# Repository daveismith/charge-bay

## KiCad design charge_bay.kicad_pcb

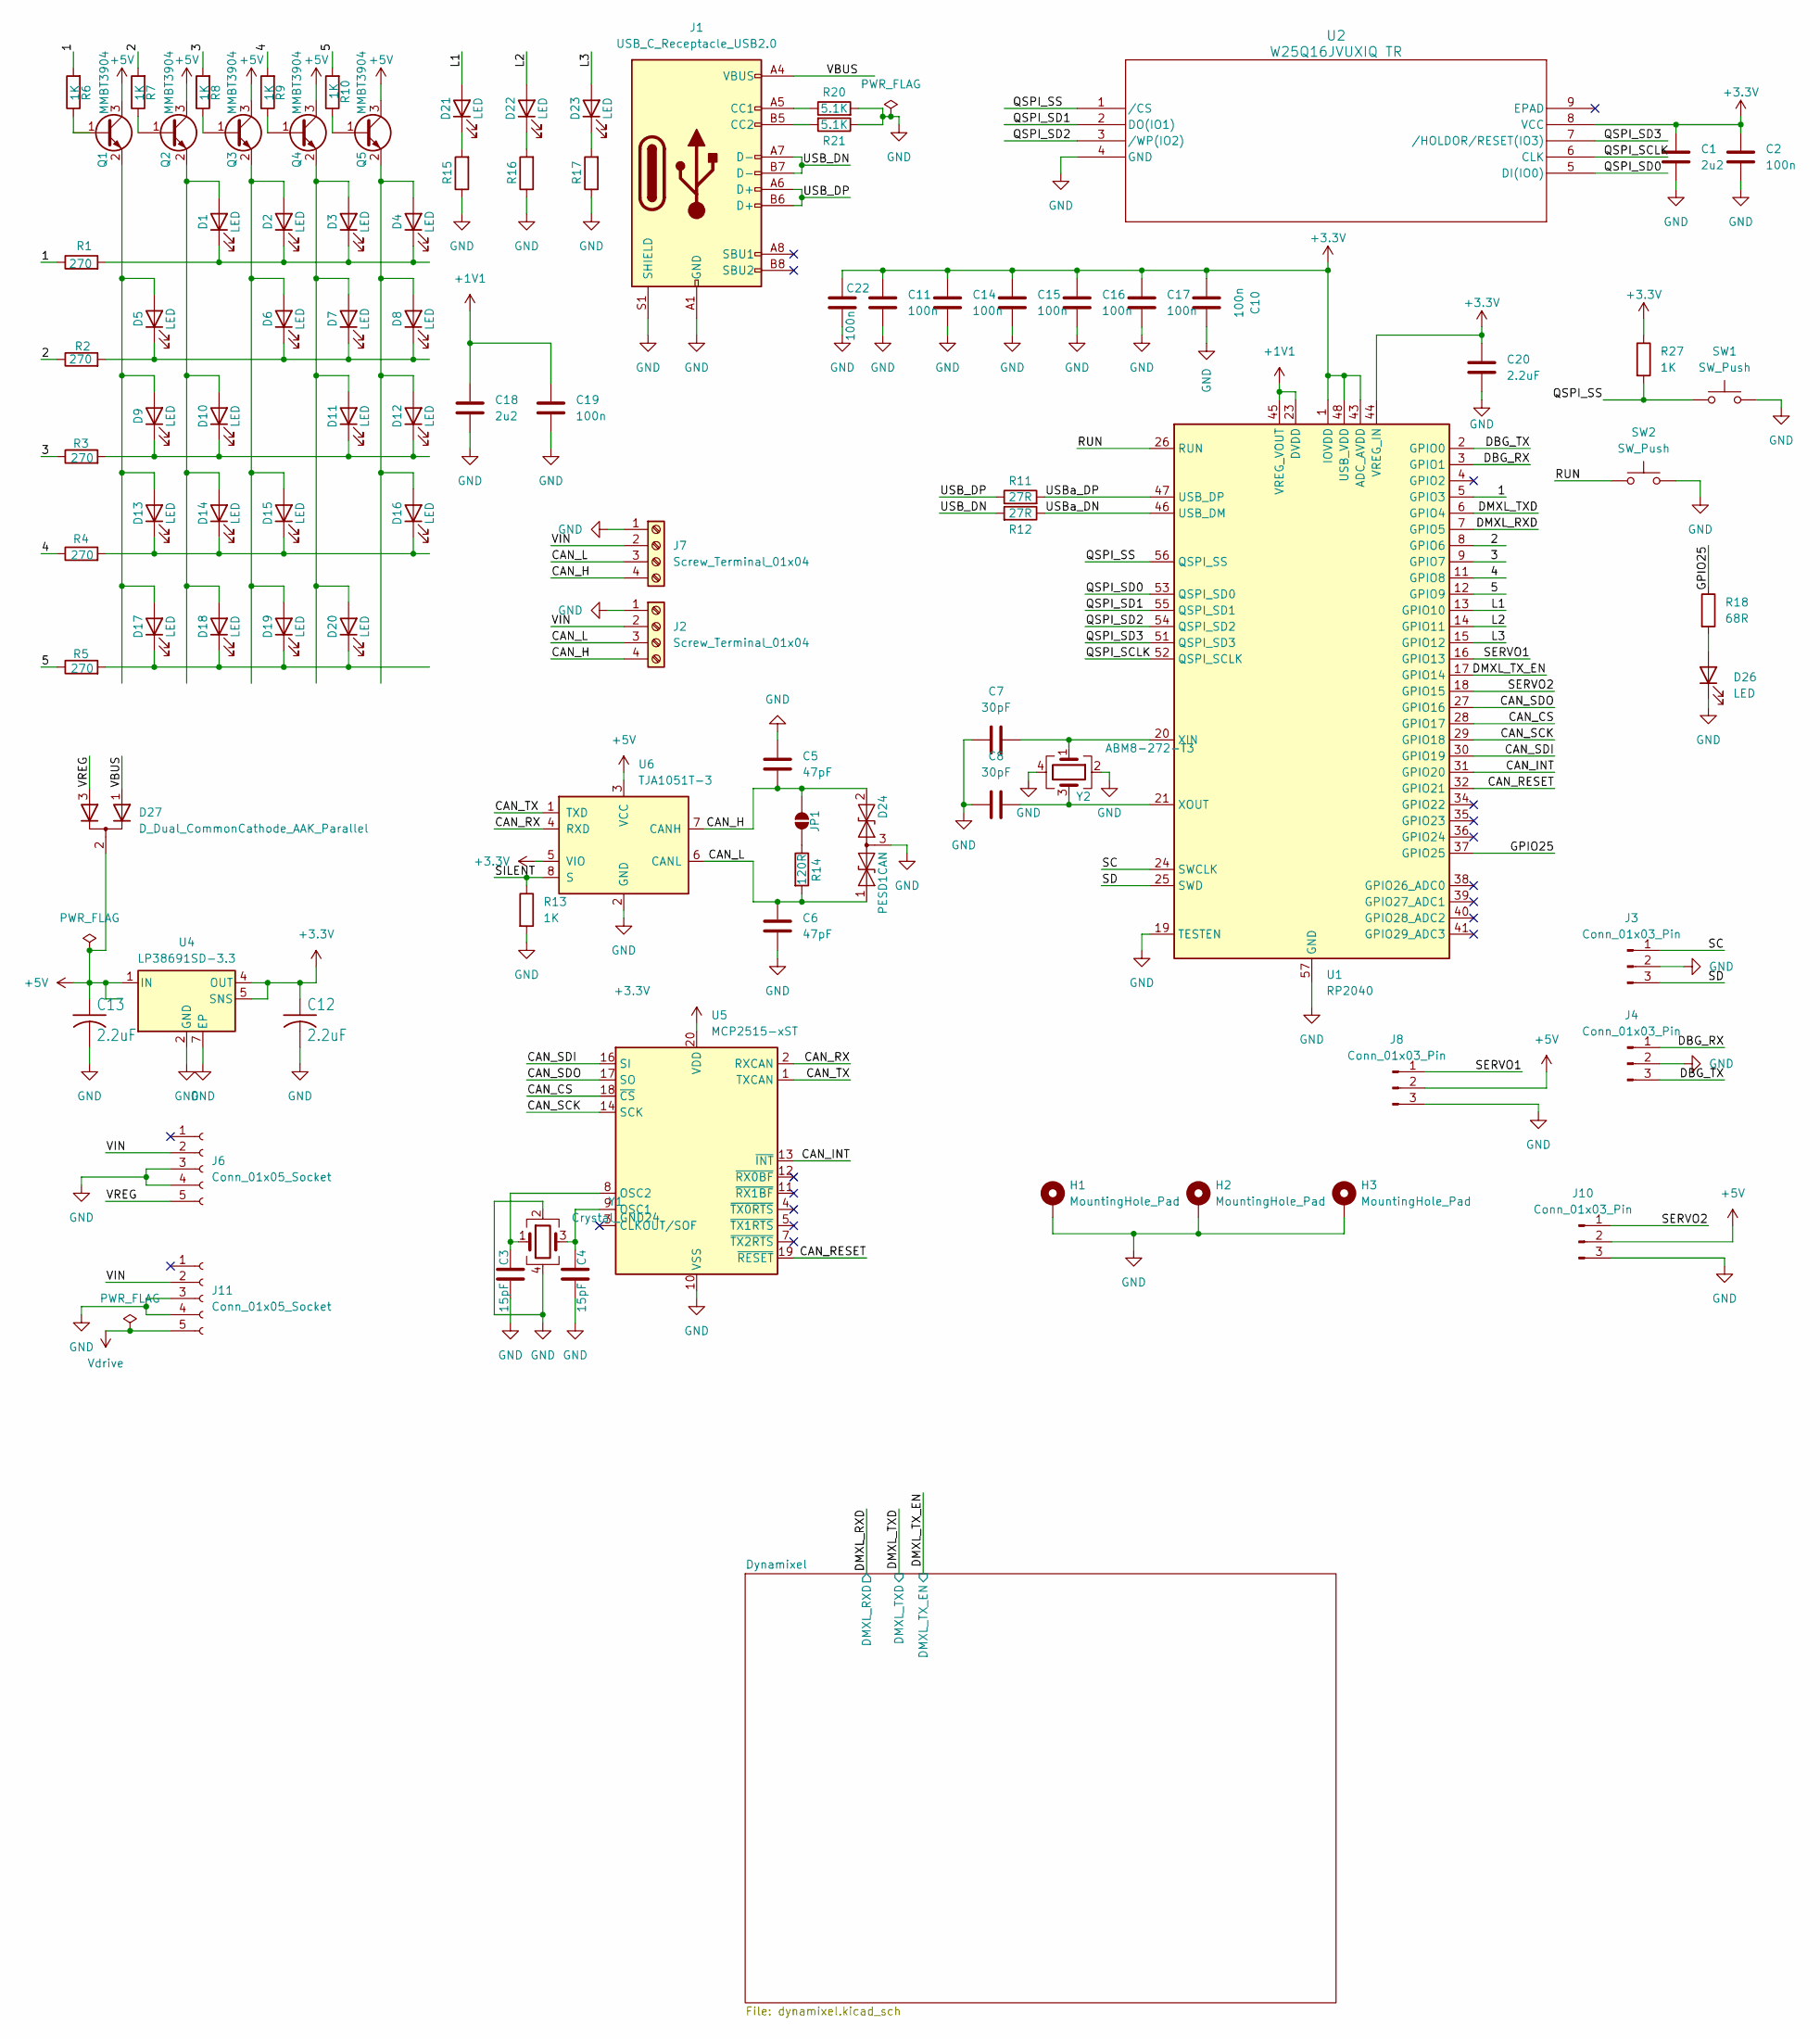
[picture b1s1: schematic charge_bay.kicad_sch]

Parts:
C1, C18: 2u2; C_0402_1005Metric; JLCPCB C12530
C2, C10, C11, C14, C15, C16, C17, C19, C22: 100n; C_0402_1005Metric; JLCPCB C1525
C3, C4: 15pF; C_0603_1608Metric; JLCPCB C1644
C5, C6: 47pF; C_0603_1608Metric; JLCPCB C1671
C7, C8: 30pF; C_0603_1608Metric; JLCPCB C1658
C12, C20: 2.2uF; C_0402_1005Metric; JLCPCB C12530
C13: 2.2uF; C_0603_1608Metric; JLCPCB C23630
D1, D2, D3, D4, D5, D6, D7, D8, D9, D10, D11, D12, D13, D14, D15, D16, D17, D18, D19, D20, D21, D22, D23: LED; LED_D3.0mm
D24: PESD1CAN; SOT-23; JLCPCB C284094
D26: LED; LED_0603_1608Metric; JLCPCB C2286
D27: D_Dual_CommonCathode_AAK_Parallel; SOT-223-3_TabPin2; JLCPCB C260229
H1, H2, H3: MountingHole_Pad; MountingHole_3.2mm_M3_DIN965_Pad_TopBottom
J1: USB_C_Receptacle_USB2.0; USB_C_Receptacle_G-Switch_GT-USB-7010ASV; JLCPCB C2988369
J2, J7: Screw_Terminal_01x04; TerminalBlock_Phoenix_PT-1,5-4-3.5-H_1x04_P3.50mm_Horizontal
J3, J4: Conn_01x03_Pin; JST_SH_BM03B-SRSS-TB_1x03-1MP_P1.00mm_Vertical
J6, J11: Conn_01x05_Socket; PinSocket_1x05_P2.54mm_Vertical
J8, J10: Conn_01x03_Pin; PinHeader_1x03_P2.54mm_Vertical
JP1: SolderJumper_2_Open; SolderJumper-2_P1.3mm_Open_TrianglePad1.0x1.5mm
Q1, Q2, Q3, Q4, Q5: MMBT3904; SOT-23; JLCPCB C20526
R1, R2, R3, R4, R5: 270; R_0603_1608Metric; JLCPCB C22966
R6, R7, R8, R9, R10, R13, R15, R16, R17, R27: 1K; R_0402_1005Metric; JLCPCB C11702
R11, R12: 27R; R_0402_1005Metric; JLCPCB C25100
R14: 120R; R_0402_1005Metric; JLCPCB C25079
R18: 68R; R_0402_1005Metric; JLCPCB C25131
R20, R21: 5.1K; R_0402_1005Metric; JLCPCB C25905
SW1, SW2: SW_Push; SW_Push_1P1T_XKB_TS-1187A; JLCPCB C318884
U1: RP2040; QFN-56-1EP_7x7mm_P0.4mm_EP3.2x3.2mm; JLCPCB C2040
U2: W25Q16JVUXIQ TR; USON-8_UX_2x3x0p6_WIN; JLCPCB C2843335
U4: LP38691SD-3.3; WSON-6-1EP_3x3mm_P0.95mm; JLCPCB C2876186
U5: MCP2515-xST; TSSOP-20_4.4x6.5mm_P0.65mm; JLCPCB C15193
U6: TJA1051T-3; SOIC-8_3.9x4.9mm_P1.27mm; JLCPCB C38695
Y1: Crystal_GND24; Crystal_SMD_Abracon_ABM8G-4Pin_3.2x2.5mm; JLCPCB C13738
Y2: ABM8-272-T3; Crystal_SMD_Abracon_ABM8G-4Pin_3.2x2.5mm; JLCPCB C9002

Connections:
+1V1: C18.1, C19.1, U1.23 (DVDD), U1.45 (VREG_VOUT), U1.50 (DVDD)
+3.3V: C1.1, C2.1, C10.1, C11.2, C12.1, C14.2, C15.2, C16.2, C17.2, C20.1, C22.2, R27.1, U1.1 (IOVDD), U1.10 (IOVDD), U1.22 (IOVDD), U1.33 (IOVDD), U1.42 (IOVDD), U1.43 (ADC_AVDD), U1.44 (VREG_IN), U1.48 (USB_VDD), U1.49 (IOVDD), U2.8 (VCC), U4.4 (OUT), U4.5 (SNS), U5.20 (VDD), U6.5 (VIO); also elsewhere on the board
+5V: C13.1, D27.2 (K), J8.2, J10.2, Q1.3 (C), Q2.3 (C), Q3.3 (C), Q4.3 (C), Q5.3 (C), U4.1 (IN), U4.6 (IN), U6.3 (VCC); also elsewhere on the board
/1: R1.1, R6.2, U1.5 (GPIO3)
/2: R2.1, R7.2, U1.8 (GPIO6)
/3: R3.1, R8.2, U1.9 (GPIO7)
/4: R4.1, R9.2, U1.11 (GPIO8)
/5: R5.1, R10.2, U1.12 (GPIO9)
/CAN_CS: U1.28 (GPIO17), U5.18 (~CS)
/CAN_H: C5.2, D24.2 (A2), J2.4, J7.4, JP1.2 (B), U6.7 (CANH)
/CAN_INT: U1.31 (GPIO20), U5.13 (~INT)
/CAN_L: C6.1, D24.1 (A1), J2.3, J7.3, R14.2, U6.6 (CANL)
/CAN_RESET: U1.32 (GPIO21), U5.19 (~RESET)
/CAN_RX: U5.2 (RXCAN), U6.4 (RXD)
/CAN_SCK: U1.29 (GPIO18), U5.14 (SCK)
/CAN_SDI: U1.30 (GPIO19), U5.16 (SI)
/CAN_SDO: U1.27 (GPIO16), U5.17 (SO)
/CAN_TX: U5.1 (TXCAN), U6.1 (TXD)
/DBG_RX: J4.1, U1.3 (GPIO1)
/DBG_TX: J4.3, U1.2 (GPIO0)
/DMXL_RXD: U1.7 (GPIO5); also elsewhere on the board
/DMXL_TXD: U1.6 (GPIO4); also elsewhere on the board
/DMXL_TX_EN: U1.17 (GPIO14); also elsewhere on the board
/GPIO25: R18.1, U1.37 (GPIO25)
/L1: D21.2 (A), U1.13 (GPIO10)
/L2: D22.2 (A), U1.14 (GPIO11)
/L3: D23.2 (A), U1.15 (GPIO12)
/QSPI_SCLK: U1.52 (QSPI_SCLK), U2.6 (CLK)
/QSPI_SD0: U1.53 (QSPI_SD0), U2.5 (DI(IO0))
/QSPI_SD1: U1.55 (QSPI_SD1), U2.2 (DO(IO1))
/QSPI_SD2: U1.54 (QSPI_SD2), U2.3 (/WP(IO2))
/QSPI_SD3: U1.51 (QSPI_SD3), U2.7 (/HOLDOR/RESET(IO3))
/QSPI_SS: R27.2, SW1.1, U1.56 (QSPI_SS), U2.1 (/CS)
/RUN: SW2.1, U1.26 (RUN)
/SC: J3.1, U1.24 (SWCLK)
/SD: J3.3, U1.25 (SWD)
/SERVO1: J8.1, U1.16 (GPIO13)
/SERVO2: J10.1, U1.18 (GPIO15)
/SILENT: R13.1, U6.8 (S)
/USB_DN: J1.A7 (D-), J1.B7 (D-), R12.2
/USB_DP: J1.A6 (D+), J1.B6 (D+), R11.1
/USBa_DN: R12.1, U1.46 (USB_DM)
/USBa_DP: R11.2, U1.47 (USB_DP)
/VBUS: D27.1 (A), J1.A4 (VBUS), J1.A9 (VBUS), J1.B4 (VBUS), J1.B9 (VBUS)
/VIN: J2.2, J6.2, J7.2, J11.2
/VREG: D27.3 (A), J6.5
GND: C1.2, C2.2, C3.2, C4.2, C5.1, C6.2, C7.1, C8.1, C10.2, C11.1, C12.2, C13.2, C14.1, C15.1, C16.1, C17.1, C18.2, C19.2, C20.2, C22.1, D24.3 (common), D26.1 (K), H1.1, H2.1, H3.1, J1.A1 (GND), J1.A12 (GND), J1.B1 (GND), J1.B12 (GND), J1.S1 (SHIELD), J2.1, J3.2, J4.2, J6.3, J6.4, J7.1, J8.3, J10.3, J11.3, J11.4, R13.2, R15.1, R16.1, R17.1, R20.2, R21.1, SW1.2, SW2.2, U1.19 (TESTEN), U1.57 (GND), U2.4 (GND), U4.2 (GND), U4.7 (EP), U5.10 (VSS), U6.2 (GND), Y1.2, Y1.4, Y2.2, Y2.4; also elsewhere on the board
unnamed: D1.2 (A), D10.2 (A), D14.2 (A), D18.2 (A), Q2.2 (E)
unnamed: D1.1 (K), D2.1 (K), D3.1 (K), D4.1 (K), R1.2
unnamed: D5.1 (K), D6.1 (K), D7.1 (K), D8.1 (K), R2.2
unnamed: D9.1 (K), D10.1 (K), D11.1 (K), D12.1 (K), R3.2
unnamed: D3.2 (A), D7.2 (A), D11.2 (A), D20.2 (A), Q4.2 (E)
unnamed: D4.2 (A), D8.2 (A), D12.2 (A), D16.2 (A), Q5.2 (E)
unnamed: D5.2 (A), D9.2 (A), D13.2 (A), D17.2 (A), Q1.2 (E)
unnamed: D13.1 (K), D14.1 (K), D15.1 (K), D16.1 (K), R4.2
unnamed: D2.2 (A), D6.2 (A), D15.2 (A), D19.2 (A), Q3.2 (E)
unnamed: D17.1 (K), D18.1 (K), D19.1 (K), D20.1 (K), R5.2
unnamed: D21.1 (K), R15.2
unnamed: D22.1 (K), R16.2
unnamed: D23.1 (K), R17.2
unnamed: D26.2 (A), R18.2
unnamed: J1.A5 (CC1), R20.1
unnamed: J1.B5 (CC2), R21.2
unnamed: JP1.1 (A), R14.1
unnamed: Q1.1 (B), R6.1
unnamed: Q2.1 (B), R7.1
unnamed: Q3.1 (B), R8.1
unnamed: Q4.1 (B), R9.1
unnamed: Q5.1 (B), R10.1
unnamed: C7.2, U1.20 (XIN), Y2.1
unnamed: C8.2, U1.21 (XOUT), Y2.3
unnamed: C4.1, U5.9 (OSC1), Y1.3
unnamed: C3.1, U5.8 (OSC2), Y1.1
Vdrive: J11.5; also elsewhere on the board

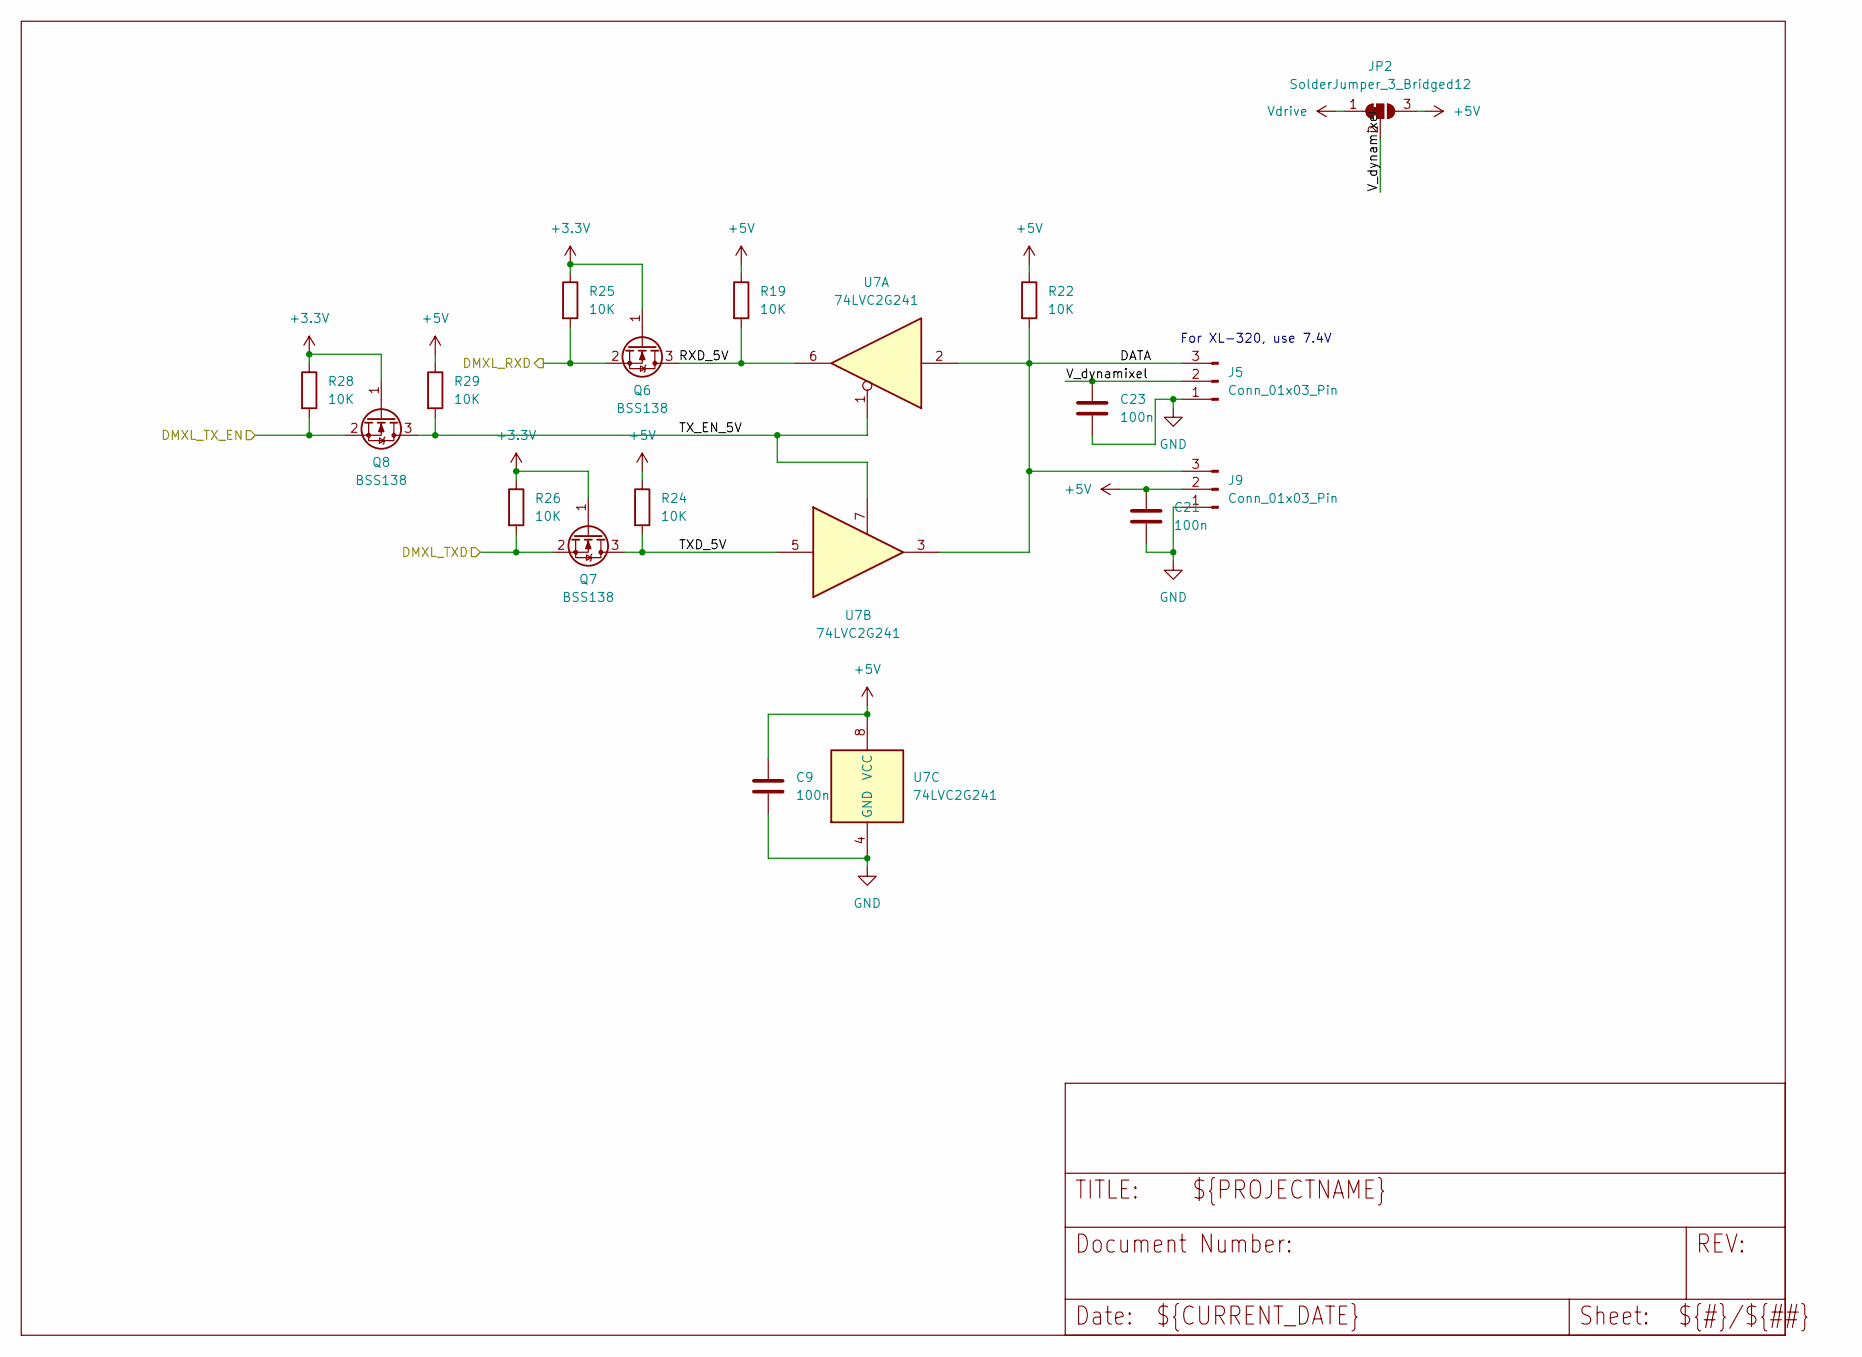
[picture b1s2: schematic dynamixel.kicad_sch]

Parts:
C9, C21, C23: 100n; C_0603_1608Metric; JLCPCB C14663
J5: Conn_01x03_Pin; Molex_Micro-Latch_53253-0370_1x03_P2.00mm_Vertical
J9: Conn_01x03_Pin; JST_EH_B3B-EH-A_1x03_P2.50mm_Vertical
JP2: SolderJumper_3_Bridged12; SolderJumper-3_P1.3mm_Bridged12_RoundedPad1.0x1.5mm
Q6, Q7, Q8: BSS138; SOT-23; JLCPCB C78284
R19, R22, R24, R25, R26, R28, R29: 10K; R_0402_1005Metric; JLCPCB C25744
U7: 74LVC2G241; VSSOP-8_2.3x2mm_P0.5mm; JLCPCB C10430

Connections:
+3.3V: Q6.1 (G), Q7.1 (G), Q8.1 (G), R25.1, R26.1, R28.1; also elsewhere on the board
+5V: C9.1, C21.1, J9.2, JP2.3 (B), R19.1, R22.1, R24.1, R29.1, U7.8 (VCC); also elsewhere on the board
/DMXL_RXD: Q6.2 (S), R25.2; also elsewhere on the board
/DMXL_TXD: Q7.2 (S), R26.2; also elsewhere on the board
/DMXL_TX_EN: Q8.2 (S), R28.2; also elsewhere on the board
/Dynamixel/DATA: J5.3, J9.3, R22.2, U7.2, U7.3
/Dynamixel/RXD_5V: Q6.3 (D), R19.2, U7.6
/Dynamixel/TXD_5V: Q7.3 (D), R24.2, U7.5
/Dynamixel/TX_EN_5V: Q8.3 (D), R29.2, U7.1, U7.7
/Dynamixel/V_dynamixel: C23.1, J5.2, JP2.2 (C)
GND: C9.2, C21.2, C23.2, J5.1, J9.1, U7.4 (GND); also elsewhere on the board
Vdrive: JP2.1 (A); also elsewhere on the board

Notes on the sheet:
For XL-320, use 7.4V

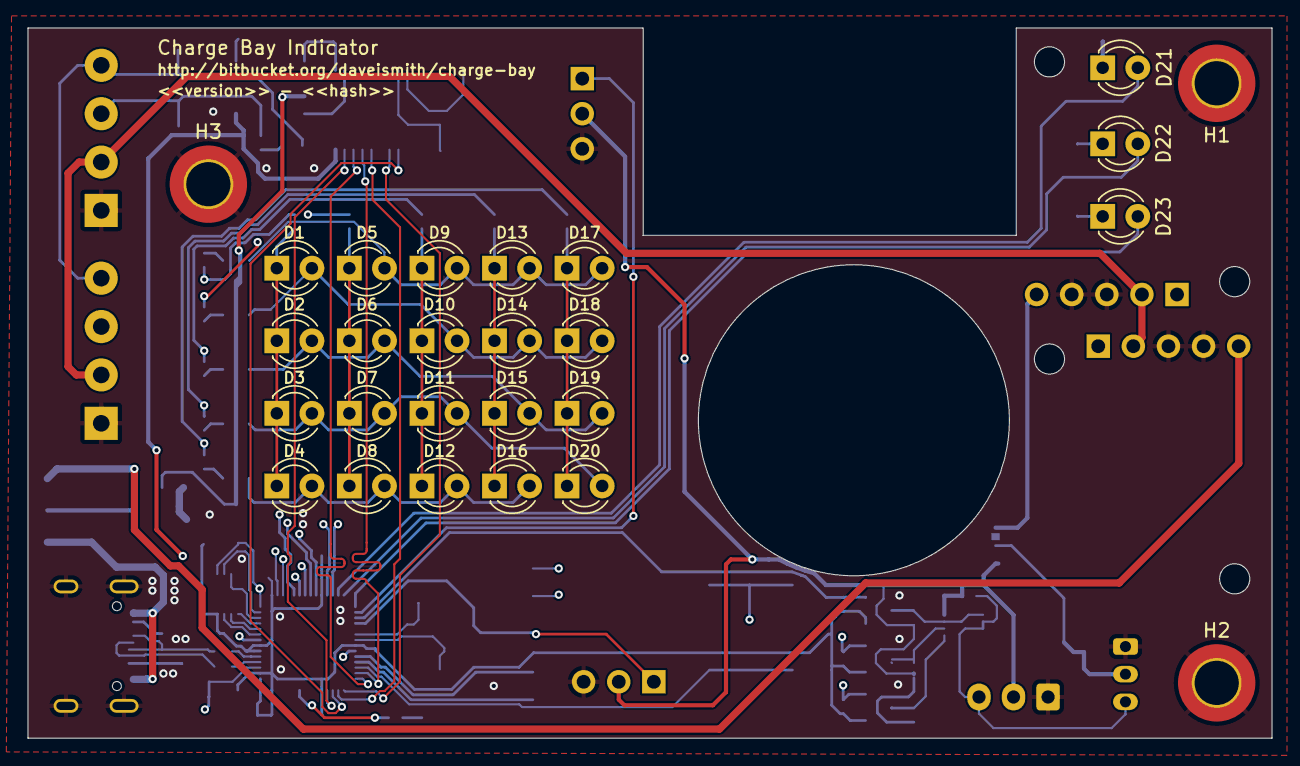
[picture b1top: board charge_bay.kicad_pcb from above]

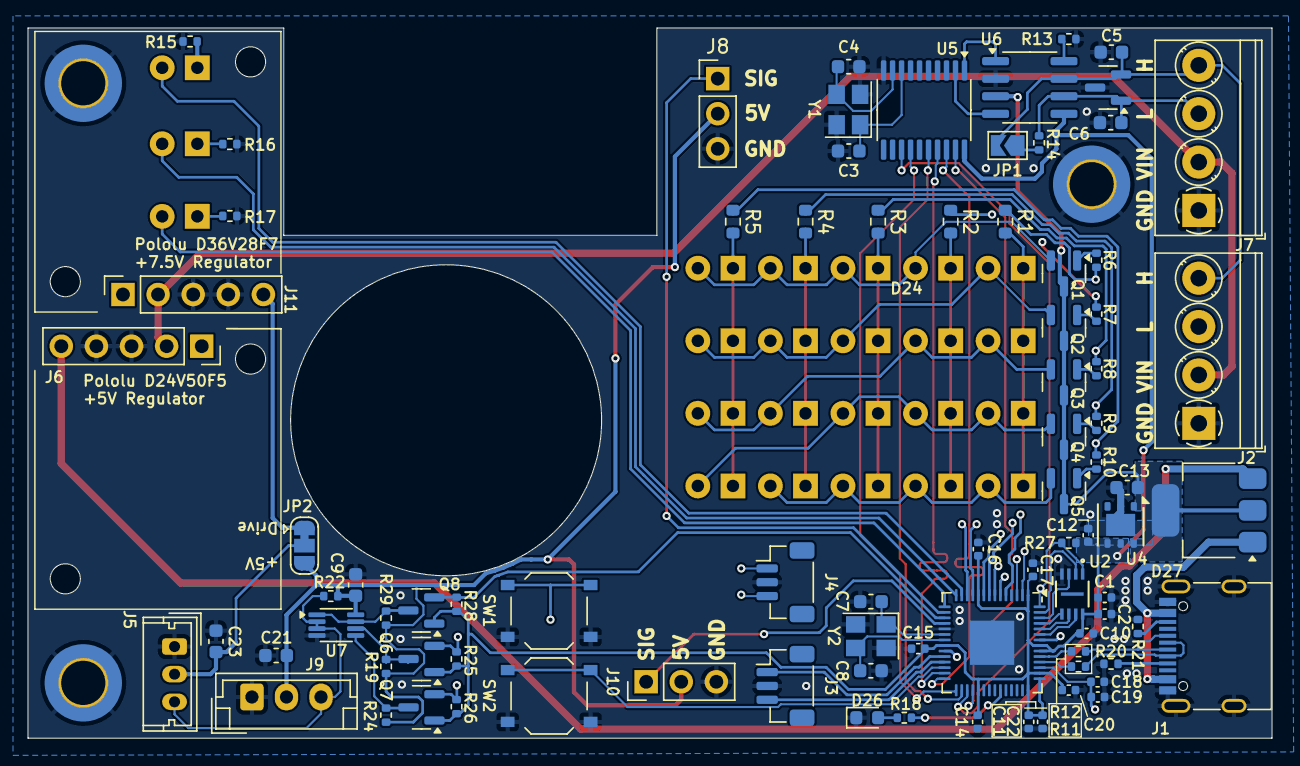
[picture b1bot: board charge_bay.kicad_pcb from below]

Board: 4 copper layers, 90.0 x 51.4 mm, 111 parts (85 on the bottom side), 79 nets.

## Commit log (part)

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2025-01-03 Adding Action to build exports.
2025-01-03 Adding missing file
2025-01-04 Update to swap to basic for MMBT3904 transistors
2025-01-04 Adding Rotations
2025-01-04 Adjustments for Generation
2025-01-04 Trying to adjust VSSOP and Q6-Q8
2025-01-04 Update KiBot Reference
2025-01-04 Update References.
2025-01-04 Update SOT-223-3 & Q6-Q8
2025-01-04 Adds Regulator & adjusts rotation on Y2, D24, U1, U2 & U5
2025-01-04 Update U4 & U5 Rotations
2025-01-04 Update U2 & U4
2025-01-04 Update Silkscreen With Pololu Parts
2025-01-05 Fixing 10K Part Number
2025-01-05 Update Silkscreen With Pololu Parts, etc.
